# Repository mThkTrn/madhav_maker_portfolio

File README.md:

# 👋 Hello! I'm Madhav

Welcome to my maker portfolio! This repository serves as a consolidated showcase of my various projects. Each project has its own directory with its source code and documentation.

## Projects

### [Forj](/Forj)

### [Quiz Bowl Platform](/QuizBowlPlatform)

### [RoboCup Robot](/RoboCupRobot)

### [TrinHub](/TrinHub)

### [Vaach](/Vaach)

### [Wannagram](/Wannagram)

### [Macrocycle Design](/MacrocycleDesign)

### [Liver Annotation](/LiverAnnotation)

### [Writeboard](/Writeboard)

## Notes
- Each project directory contains its own README with more specific details about setup and usage.
- While many of these projects have their own GitHub repositories with committ histories, I was not able to share those repositories due to my collaborators' privacy concerns.

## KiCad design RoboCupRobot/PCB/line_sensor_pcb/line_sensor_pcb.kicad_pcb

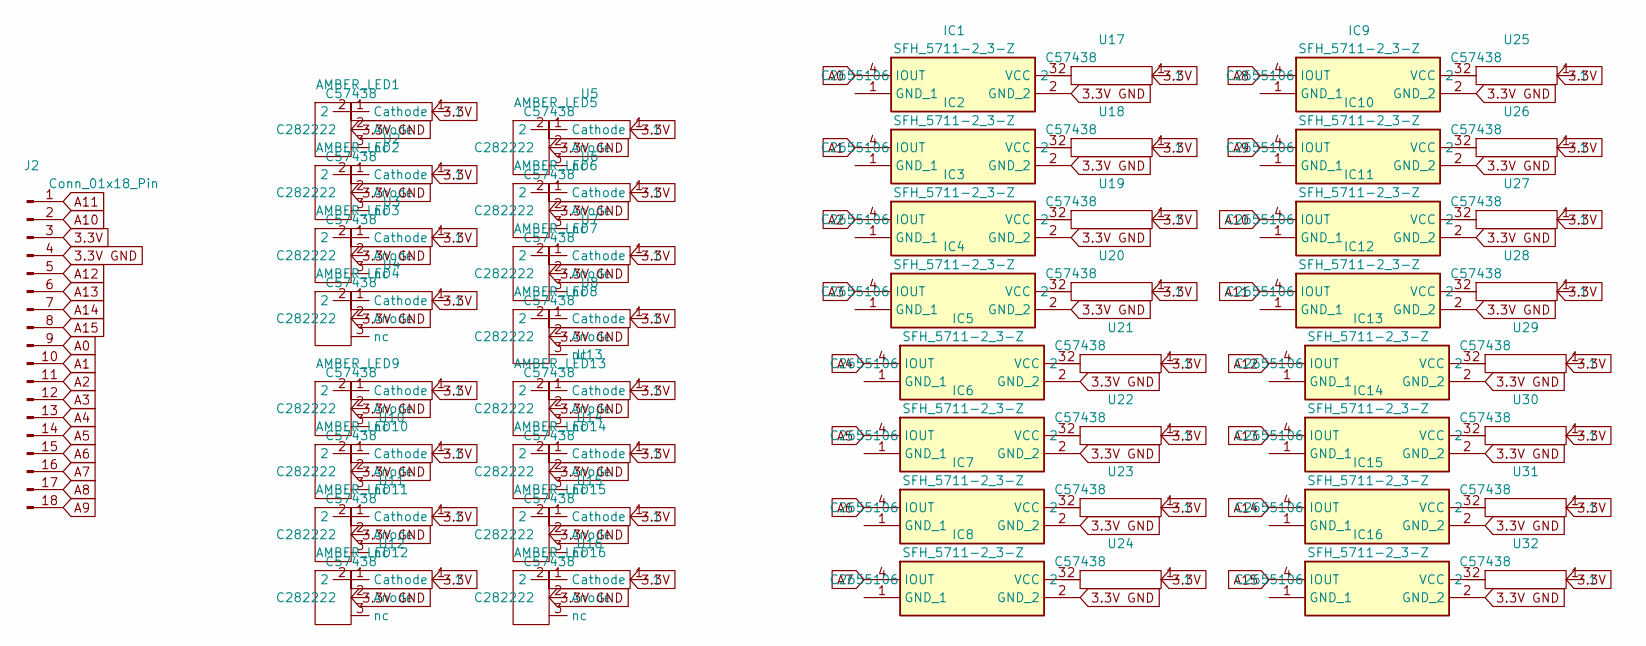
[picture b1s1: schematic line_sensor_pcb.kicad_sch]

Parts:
AMBER_LED1, AMBER_LED2, AMBER_LED3, AMBER_LED4, AMBER_LED5, AMBER_LED6, AMBER_LED7, AMBER_LED8, AMBER_LED9, AMBER_LED10, AMBER_LED11, AMBER_LED12, AMBER_LED13, AMBER_LED14, AMBER_LED15, AMBER_LED16: ELSW-F41Y1-OLPNM-AA3A5 amber led; LCSC C282222
IC1, IC2, IC3, IC4, IC5, IC6, IC7, IC8, IC9, IC10, IC11, IC12, IC13, IC14, IC15, IC16: SFH_5711-2_3-Z; SFH571123Z; Mouser Part Number 720-SFH5711-2/3-Z
J2: Conn_01x18_Pin; TE_1-87465-9
U1, U2, U3, U4, U5, U6, U7, U8, U9, U10, U11, U12, U13, U14, U15, U16, U17, U18, U19, U20, U21, U22, U23, U24, U25, U26, U27, U28, U29, U30, U31, U32: general_resistor; LCSC C57438

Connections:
3.3V: J2.3, U1.1, U2.1, U3.1, U4.1, U5.1, U6.1, U7.1, U8.1, U9.1, U10.1, U11.1, U12.1, U13.1, U14.1, U15.1, U16.1, U17.1, U18.1, U19.1, U20.1, U21.1, U22.1, U23.1, U24.1, U25.1, U26.1, U27.1, U28.1, U29.1, U30.1, U31.1, U32.1
3.3V GND: AMBER_LED1.2 (Anode), AMBER_LED2.2 (Anode), AMBER_LED3.2 (Anode), AMBER_LED4.2 (Anode), AMBER_LED5.2 (Anode), AMBER_LED6.2 (Anode), AMBER_LED7.2 (Anode), AMBER_LED8.2 (Anode), AMBER_LED9.2 (Anode), AMBER_LED10.2 (Anode), AMBER_LED11.2 (Anode), AMBER_LED12.2 (Anode), AMBER_LED13.2 (Anode), AMBER_LED14.2 (Anode), AMBER_LED15.2 (Anode), AMBER_LED16.2 (Anode), IC1.2 (GND_2), IC2.2 (GND_2), IC3.2 (GND_2), IC4.2 (GND_2), IC5.2 (GND_2), IC6.2 (GND_2), IC7.2 (GND_2), IC8.2 (GND_2), IC9.2 (GND_2), IC10.2 (GND_2), IC11.2 (GND_2), IC12.2 (GND_2), IC13.2 (GND_2), IC14.2 (GND_2), IC15.2 (GND_2), IC16.2 (GND_2), J2.4
A0: IC1.4 (IOUT), J2.9
A1: IC2.4 (IOUT), J2.10
A2: IC3.4 (IOUT), J2.11
A3: IC4.4 (IOUT), J2.12
A4: IC5.4 (IOUT), J2.13
A5: IC6.4 (IOUT), J2.14
A6: IC7.4 (IOUT), J2.15
A7: IC8.4 (IOUT), J2.16
A8: IC9.4 (IOUT), J2.17
A9: IC10.4 (IOUT), J2.18
A10: IC11.4 (IOUT), J2.2
A11: IC12.4 (IOUT), J2.1
A12: IC13.4 (IOUT), J2.5
A13: IC14.4 (IOUT), J2.6
A14: IC15.4 (IOUT), J2.7
A15: IC16.4 (IOUT), J2.8
unnamed: AMBER_LED1.1 (Cathode), U1.2
unnamed: AMBER_LED2.1 (Cathode), U2.2
unnamed: AMBER_LED3.1 (Cathode), U3.2
unnamed: AMBER_LED4.1 (Cathode), U4.2
unnamed: AMBER_LED5.1 (Cathode), U5.2
unnamed: AMBER_LED6.1 (Cathode), U6.2
unnamed: AMBER_LED7.1 (Cathode), U7.2
unnamed: AMBER_LED8.1 (Cathode), U8.2
unnamed: AMBER_LED9.1 (Cathode), U9.2
unnamed: AMBER_LED10.1 (Cathode), U10.2
unnamed: AMBER_LED11.1 (Cathode), U11.2
unnamed: AMBER_LED12.1 (Cathode), U12.2
unnamed: AMBER_LED13.1 (Cathode), U13.2
unnamed: AMBER_LED14.1 (Cathode), U14.2
unnamed: AMBER_LED15.1 (Cathode), U15.2
unnamed: AMBER_LED16.1 (Cathode), U16.2
unnamed: IC1.3 (VCC), U17.2
unnamed: IC2.3 (VCC), U18.2
unnamed: IC3.3 (VCC), U19.2
unnamed: IC4.3 (VCC), U20.2
unnamed: IC5.3 (VCC), U21.2
unnamed: IC6.3 (VCC), U22.2
unnamed: IC7.3 (VCC), U23.2
unnamed: IC8.3 (VCC), U24.2
unnamed: IC9.3 (VCC), U25.2
unnamed: IC10.3 (VCC), U26.2
unnamed: IC11.3 (VCC), U27.2
unnamed: IC12.3 (VCC), U28.2
unnamed: IC13.3 (VCC), U29.2
unnamed: IC14.3 (VCC), U30.2
unnamed: IC15.3 (VCC), U31.2
unnamed: IC16.3 (VCC), U32.2

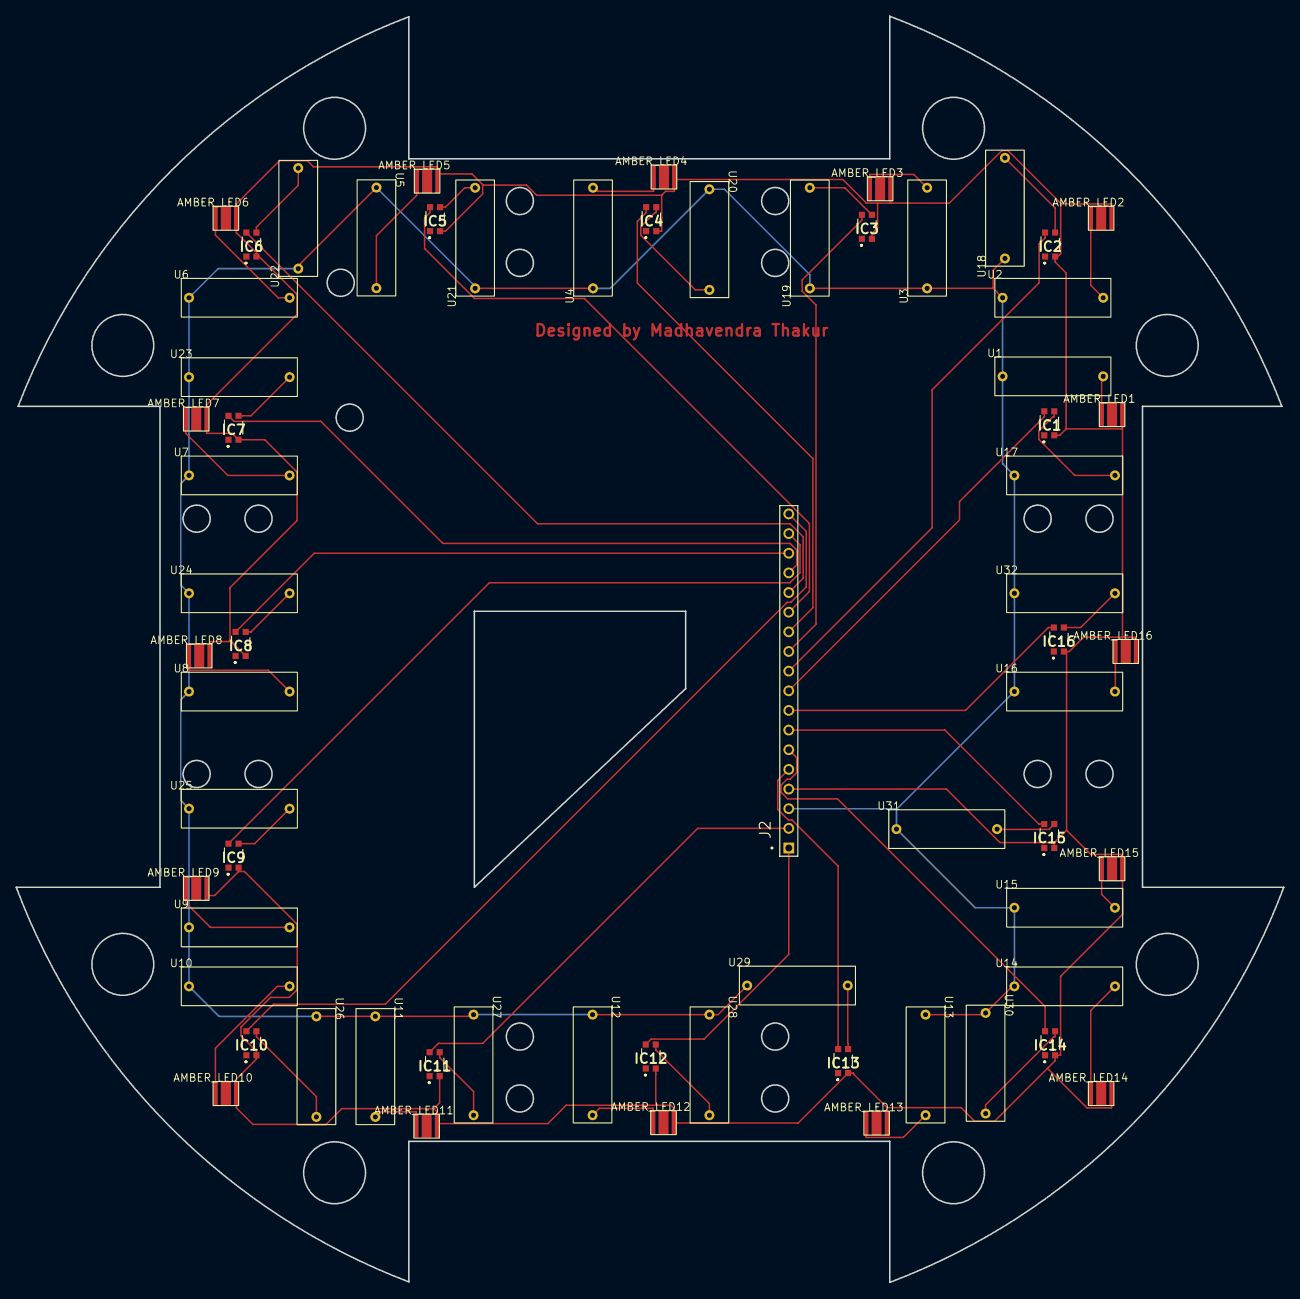
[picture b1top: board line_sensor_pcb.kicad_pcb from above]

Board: 2 copper layers, 163.8 x 163.7 mm, 65 parts (0 on the bottom side), 50 nets.

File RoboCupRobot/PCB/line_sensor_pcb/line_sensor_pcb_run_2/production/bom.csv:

Designator,Footprint,Quantity,Value,LCSC Part #
"AMBER_LED1, AMBER_LED10, AMBER_LED11, AMBER_LED12, AMBER_LED13, AMBER_LED14, AMBER_LED15, AMBER_LED16, AMBER_LED2, AMBER_LED3, AMBER_LED4, AMBER_LED5, AMBER_LED6, AMBER_LED7, AMBER_LED8, AMBER_LED9",ELSW-F41Y1-OLPNM-AA3A5 amber led,16,~,C282222
"IC1, IC10, IC11, IC12, IC13, IC14, IC15, IC16, IC2, IC3, IC4, IC5, IC6, IC7, IC8, IC9",SFH571123Z,16,SFH_5711-2_3-Z,C2655106
J2,TE_1-87465-9,1,Conn_01x18_Pin,C5142873
"U1, U10, U11, U12, U13, U14, U15, U16, U17, U18, U19, U2, U20, U21, U22, U23, U24, U25, U26, U27, U28, U29, U3, U30, U31, U32, U4, U5, U6, U7, U8, U9",general_resistor,32,~,C57438

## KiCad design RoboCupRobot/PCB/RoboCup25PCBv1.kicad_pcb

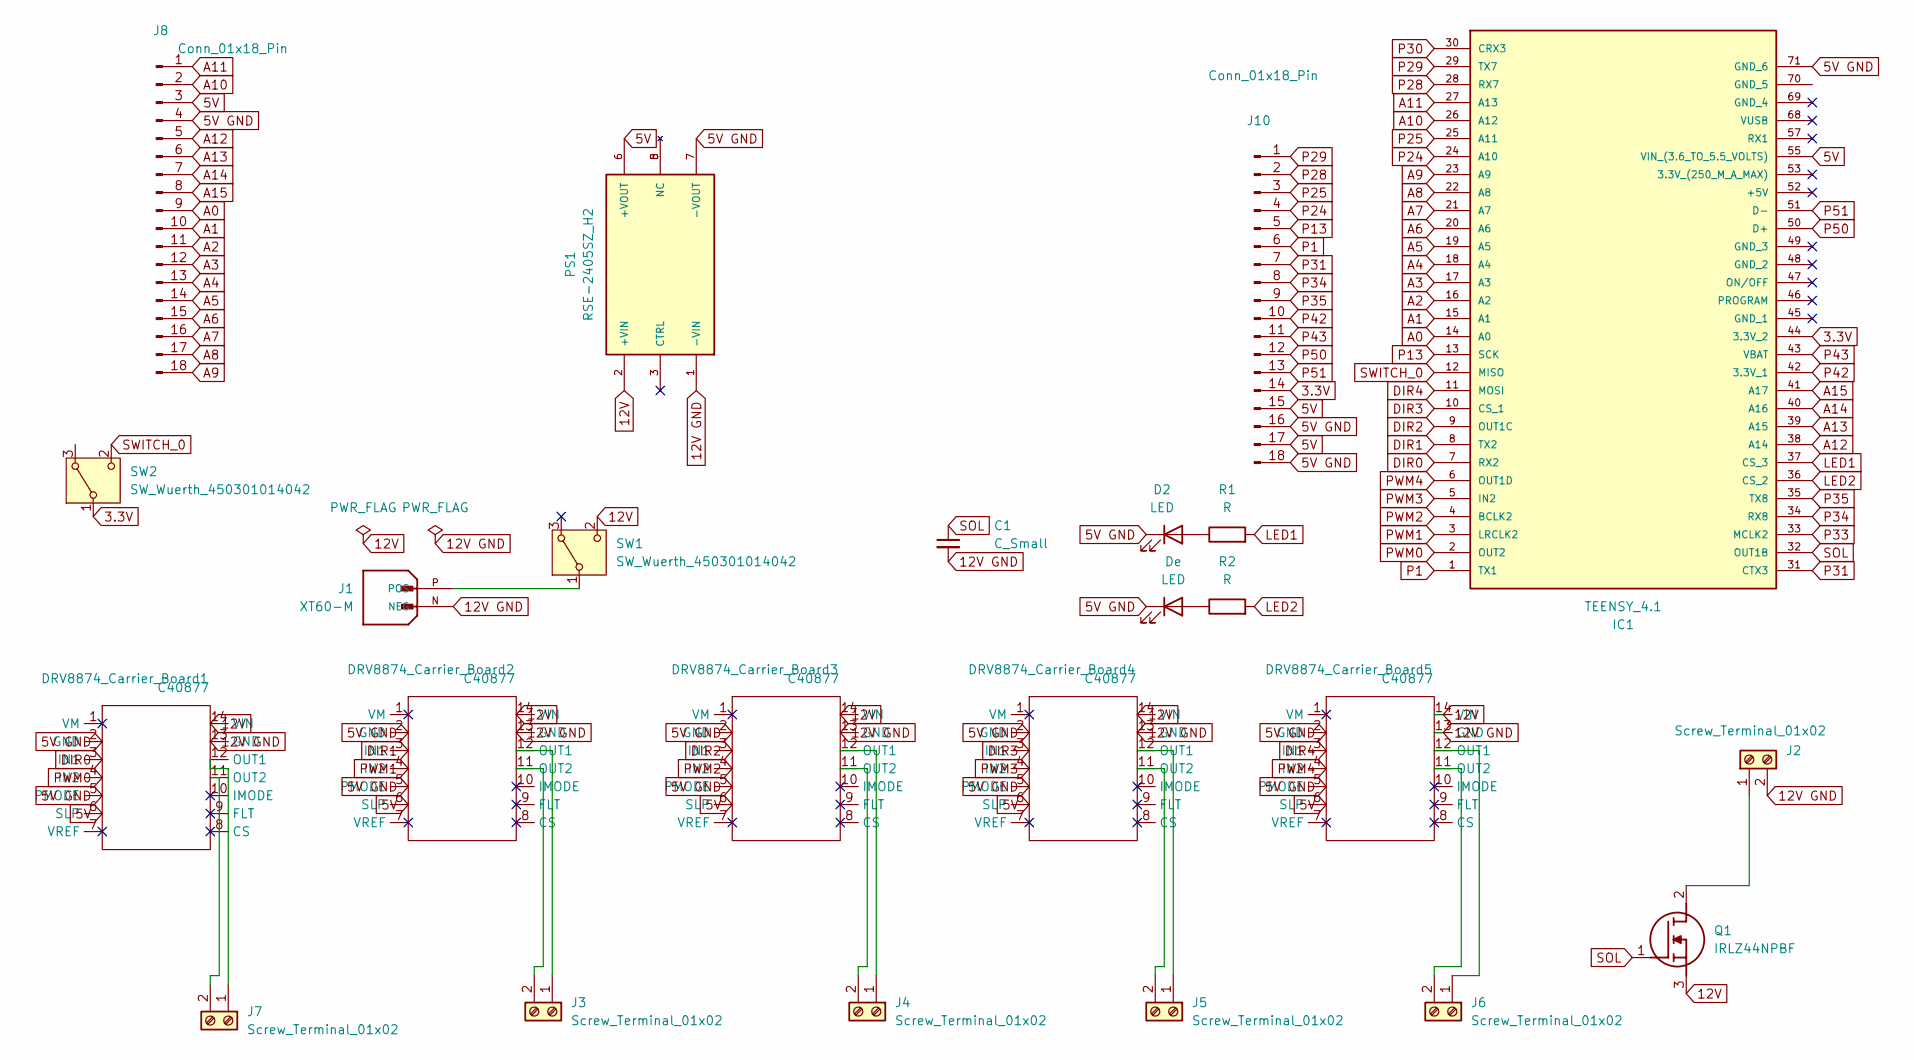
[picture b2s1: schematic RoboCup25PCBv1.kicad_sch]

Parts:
C1: C_Small; C_0201_0603Metric_Pad0.64x0.40mm_HandSolder
D2: LED; LED_D5.0mm_Horizontal_O6.35mm_Z15.0mm
DRV8874_Carrier_Board1, DRV8874_Carrier_Board2, DRV8874_Carrier_Board3, DRV8874_Carrier_Board4, DRV8874_Carrier_Board5: DRV887X; LCSC C40877
De: LED; LED_D5.0mm_Horizontal_O6.35mm_Z15.0mm
IC1: TEENSY_4.1; TEENSY41; Manufacturer_Part_Number TEENSY 4.1
J1: XT60-M; AMASS_XT60-M; PARTREV V1.2
J2, J3, J4, J5, J6, J7: Screw_Terminal_01x02; CUI_TB009-508-02BE
J8, J10: Conn_01x18_Pin; TE_1-87465-9
PS1: RSE-2405SZ_H2; CONV_RSE-2405SZ_H2; PARTREV 4/2020
Q1: IRLZ44NPBF; TO254P469X1042X1967-3P; Mouser Part Number 942-IRLZ44NPBF
R1, R2: R; R_Axial_DIN0204_L3.6mm_D1.6mm_P2.54mm_Vertical
SW1, SW2: SW_Wuerth_450301014042; rocker_switch_10a

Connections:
3.3V: IC1.44 (3.3V_2), J10.14, SW2.1 (B)
5V: DRV8874_Carrier_Board1.6 (SLP), DRV8874_Carrier_Board2.6 (SLP), DRV8874_Carrier_Board3.6 (SLP), DRV8874_Carrier_Board4.6 (SLP), DRV8874_Carrier_Board5.6 (SLP), IC1.55 (VIN_(3.6_TO_5.5_VOLTS)), J8.3, J10.15, J10.17, PS1.6 (+VOUT)
5V GND: D2.1 (K), DRV8874_Carrier_Board1.2 (GND), DRV8874_Carrier_Board1.5 (PMODE), DRV8874_Carrier_Board2.2 (GND), DRV8874_Carrier_Board2.5 (PMODE), DRV8874_Carrier_Board3.2 (GND), DRV8874_Carrier_Board3.5 (PMODE), DRV8874_Carrier_Board4.2 (GND), DRV8874_Carrier_Board4.5 (PMODE), DRV8874_Carrier_Board5.2 (GND), DRV8874_Carrier_Board5.5 (PMODE), De.1 (K), IC1.71 (GND_6), J8.4, J10.16, J10.18, PS1.7 (-VOUT); also elsewhere on the board
12V: DRV8874_Carrier_Board1.14 (VIN), DRV8874_Carrier_Board2.14 (VIN), DRV8874_Carrier_Board3.14 (VIN), DRV8874_Carrier_Board4.14 (VIN), DRV8874_Carrier_Board5.14 (VIN), PS1.2 (+VIN), Q1.3 (S), SW1.2 (C)
12V GND: C1.2, DRV8874_Carrier_Board1.13 (GND), DRV8874_Carrier_Board2.13 (GND), DRV8874_Carrier_Board3.13 (GND), DRV8874_Carrier_Board4.13 (GND), DRV8874_Carrier_Board5.13 (GND), J1.N (NEG), J2.2, PS1.1 (-VIN)
A0: IC1.14 (A0), J8.9
A1: IC1.15 (A1), J8.10
A2: IC1.16 (A2), J8.11
A3: IC1.17 (A3), J8.12
A4: IC1.18 (A4), J8.13
A5: IC1.19 (A5), J8.14
A6: IC1.20 (A6), J8.15
A7: IC1.21 (A7), J8.16
A8: IC1.22 (A8), J8.17
A9: IC1.23 (A9), J8.18
A10: IC1.26 (A12), J8.2
A11: IC1.27 (A13), J8.1
A12: IC1.38 (A14), J8.5
A13: IC1.39 (A15), J8.6
A14: IC1.40 (A16), J8.7
A15: IC1.41 (A17), J8.8
DIR0: DRV8874_Carrier_Board1.3 (IN1), IC1.7 (RX2)
DIR1: DRV8874_Carrier_Board2.3 (IN1), IC1.8 (TX2)
DIR2: DRV8874_Carrier_Board3.3 (IN1), IC1.9 (OUT1C)
DIR3: DRV8874_Carrier_Board4.3 (IN1), IC1.10 (CS_1)
DIR4: DRV8874_Carrier_Board5.3 (IN1), IC1.11 (MOSI)
LED1: IC1.37 (CS_3), R1.2
LED2: IC1.36 (CS_2), R2.2
unnamed: D2.2 (A), R1.1
unnamed 29: De.2 (A), R2.1; also elsewhere on the board
unnamed: DRV8874_Carrier_Board1.12 (OUT1), J7.1
unnamed: DRV8874_Carrier_Board1.11 (OUT2), J7.2
unnamed: DRV8874_Carrier_Board2.12 (OUT1), J3.1
unnamed: DRV8874_Carrier_Board2.11 (OUT2), J3.2
unnamed: DRV8874_Carrier_Board3.12 (OUT1), J4.1
unnamed: DRV8874_Carrier_Board3.11 (OUT2), J4.2
unnamed: DRV8874_Carrier_Board4.12 (OUT1), J5.1
unnamed: DRV8874_Carrier_Board4.11 (OUT2), J5.2
unnamed: DRV8874_Carrier_Board5.12 (OUT1), J6.1
unnamed: DRV8874_Carrier_Board5.11 (OUT2), J6.2
unnamed: J1.P (POS), SW1.1 (B)
unnamed: J2.1, Q1.2 (D)
P1: IC1.1 (TX1), J10.6
P13: IC1.13 (SCK), J10.5
P24: IC1.24 (A10), J10.4
P25: IC1.25 (A11), J10.3
P28: IC1.28 (RX7), J10.2
P29: IC1.29 (TX7), J10.1
P30: IC1.30 (CRX3)
P31: IC1.31 (CTX3), J10.7
P33: IC1.33 (MCLK2)
P34: IC1.34 (RX8), J10.8
P35: IC1.35 (TX8), J10.9
P42: IC1.42 (3.3V_1), J10.10
P43: IC1.43 (VBAT), J10.11
P50: IC1.50 (D+), J10.12
P51: IC1.51 (D-), J10.13
PWM0: DRV8874_Carrier_Board1.4 (IN2), IC1.2 (OUT2)
PWM1: DRV8874_Carrier_Board2.4 (IN2), IC1.3 (LRCLK2)
PWM2: DRV8874_Carrier_Board3.4 (IN2), IC1.4 (BCLK2)
PWM3: DRV8874_Carrier_Board4.4 (IN2), IC1.5 (IN2)
PWM4: DRV8874_Carrier_Board5.4 (IN2), IC1.6 (OUT1D)
SOL: C1.1, IC1.32 (OUT1B), Q1.1 (G)
SWITCH_0: IC1.12 (MISO), SW2.2 (C)

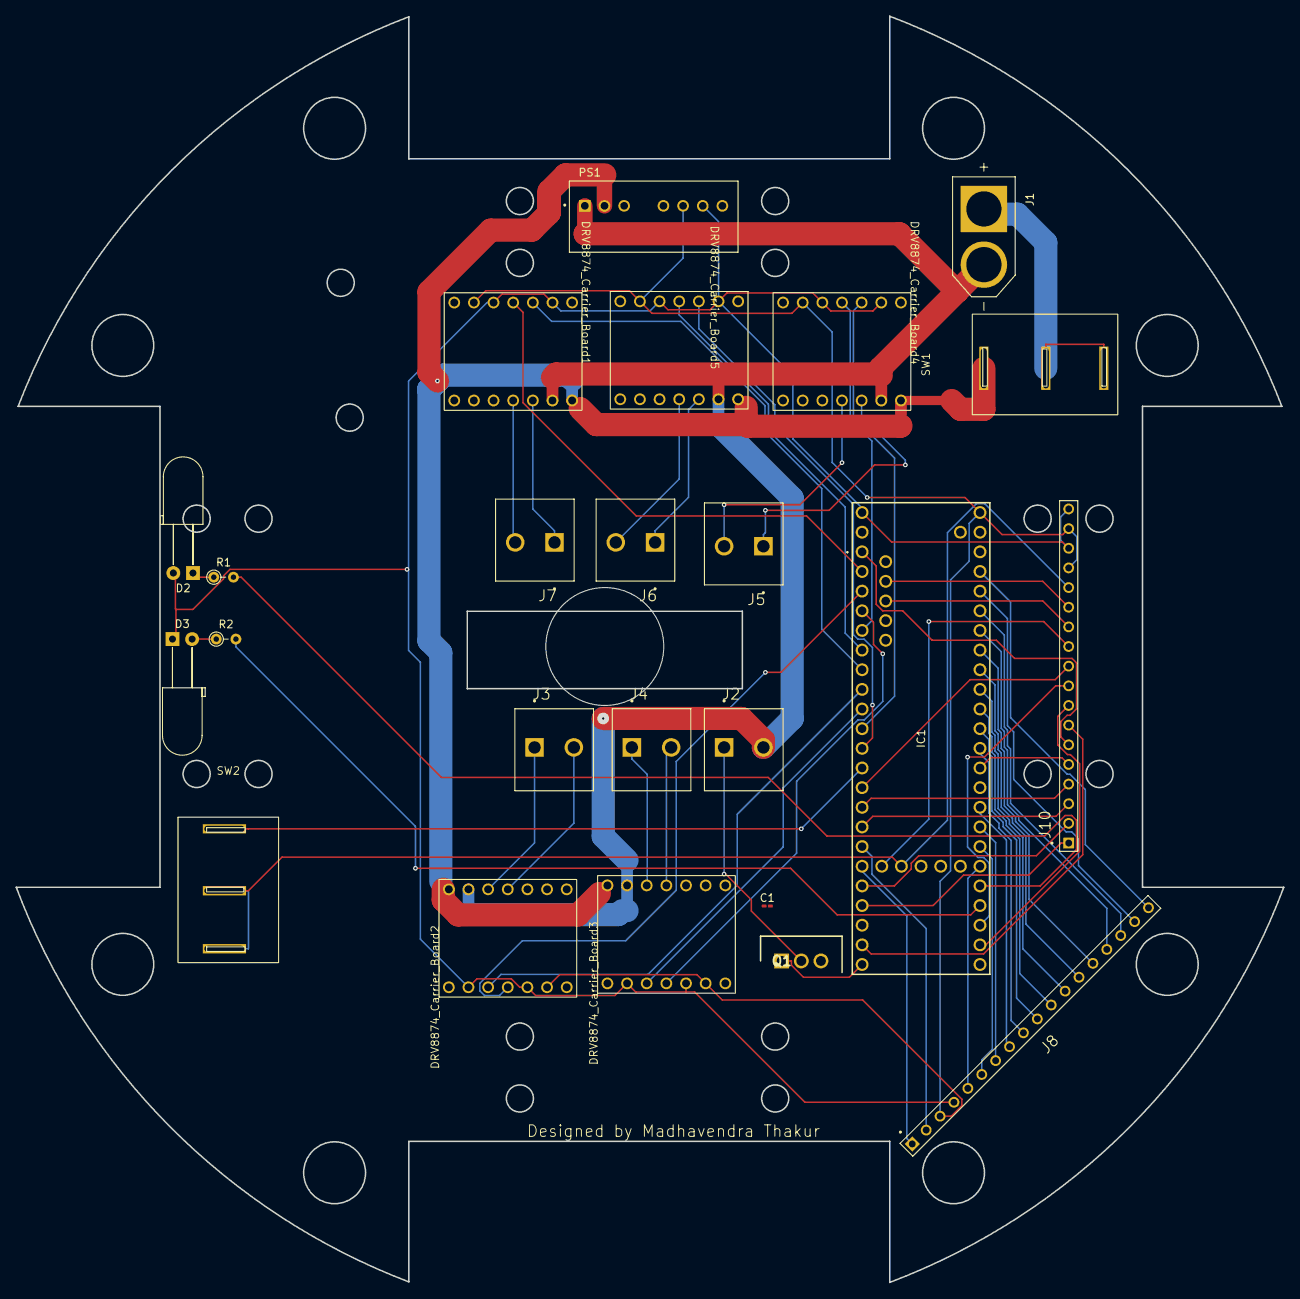
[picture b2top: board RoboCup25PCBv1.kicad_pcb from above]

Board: 2 copper layers, 163.8 x 163.7 mm, 24 parts (0 on the bottom side), 62 nets.

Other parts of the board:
D3: LED; LED_D5.0mm_Horizontal_O6.35mm_Z15.0mm

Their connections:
5V GND: D3.1 (K); also elsewhere on the board
unnamed 29: D3.2 (A); also elsewhere on the board

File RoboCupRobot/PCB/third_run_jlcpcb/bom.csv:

Designator,Footprint,Quantity,Value,LCSC Part #
C1,0201,1,C_Small,
"D2, D3",LED_D5.0mm_Horizontal_O6.35mm_Z15.0mm,2,LED,
"DRV8874_CARRIER_BOARD1, DRV8874_CARRIER_BOARD2, DRV8874_CARRIER_BOARD3, DRV8874_CARRIER_BOARD4, DRV8874_CARRIER_BOARD5",DRV887X,5,~,C40877
IC1,TEENSY41,1,TEENSY_4.1,C41376163
J1,AMASS_XT60-M,1,XT60-M,
"J10, J8",TE_1-87465-9,2,Conn_01x18_Pin,
"J2, J3, J4, J5, J6, J7",CUI_TB009-508-02BE,6,Screw_Terminal_01x02,
PS1,CONV_RSE-2405SZ_H2,1,RSE-2405SZ_H2,
Q1,TO254P469X1042X1967-3P,1,IRLZ44NPBF,
"R1, R2",R_Axial_DIN0204_L3.6mm_D1.6mm_P2.54mm_Vertical,2,R,
"SW1, SW2",rocker_switch_10a,2,SW_Wuerth_450301014042,

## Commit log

2025-10-27 Added all files with obfuscate d creds and README
2025-10-27 fixed readme links
2025-10-27 Update synthesizer.py to obfuscate secrets
2025-10-27 Convert LiverAnnotation to regular directory
2025-10-27 Convert Vaach to regular directory
2025-10-27 Convert macrocycle_design to regular directory
2025-10-27 Rename macrocycle_design to MacrocycleDesign to match project naming convention
2025-10-27 obfuscated secret
